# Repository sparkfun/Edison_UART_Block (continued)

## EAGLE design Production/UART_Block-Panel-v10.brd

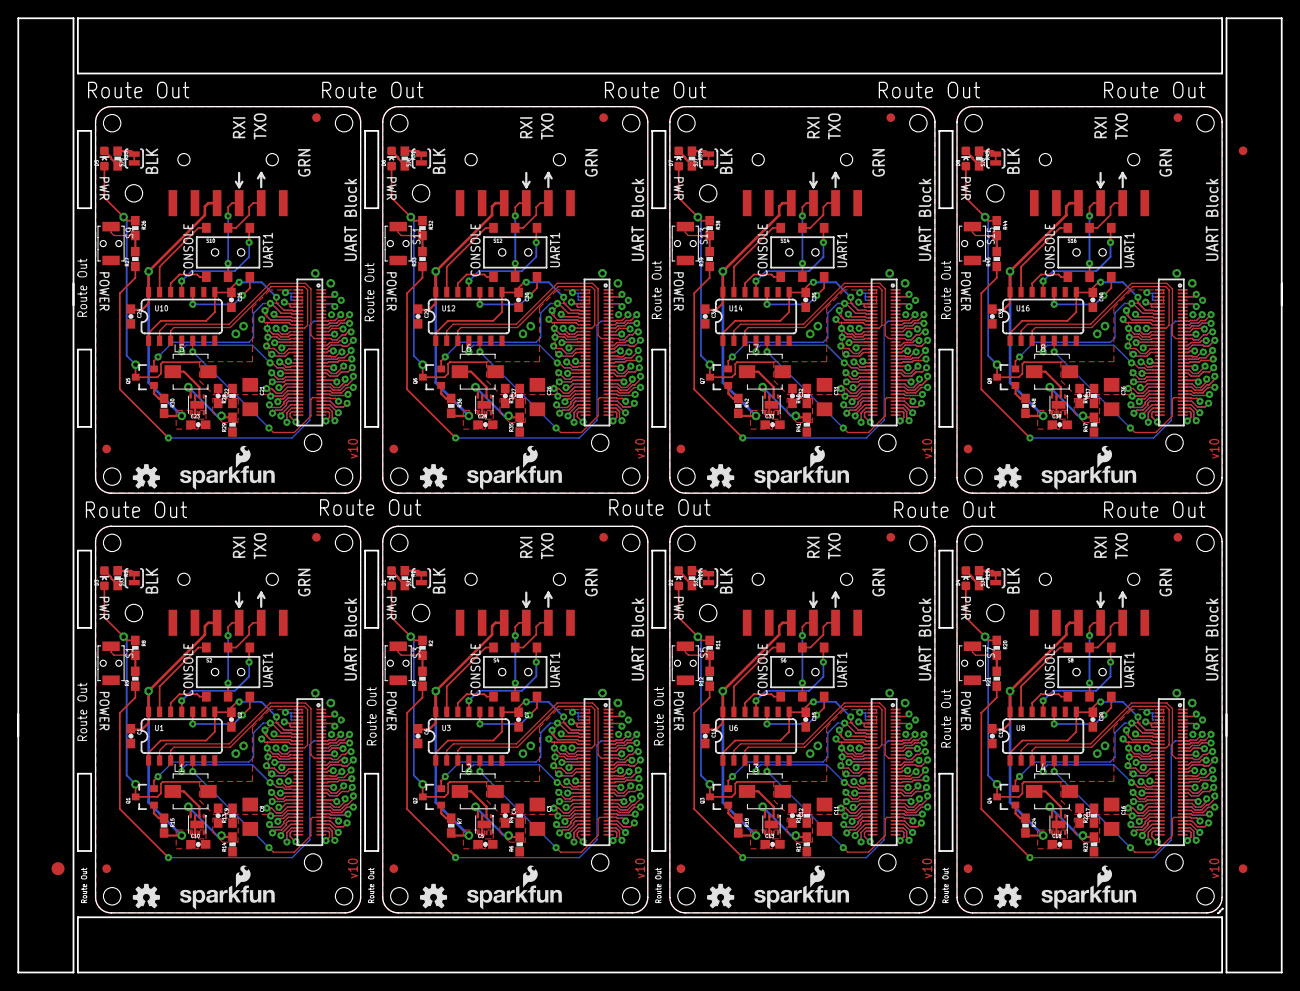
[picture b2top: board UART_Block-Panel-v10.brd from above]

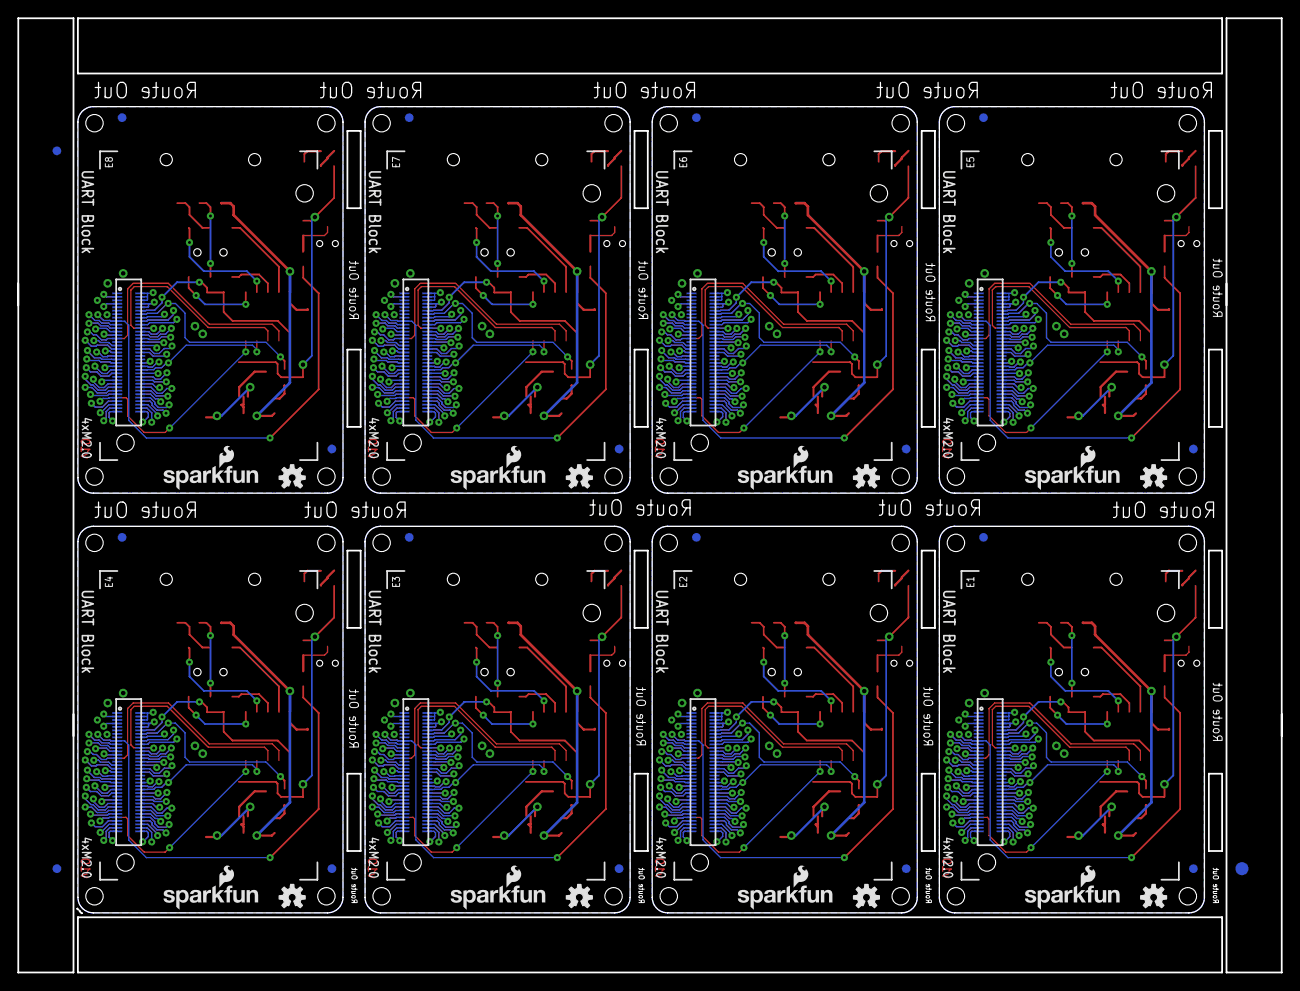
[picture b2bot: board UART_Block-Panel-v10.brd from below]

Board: 2 copper layers, 145.3 x 109.7 mm, 246 parts (51 on the bottom side), 568 nets.

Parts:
C1, C2, C6, C7, C14, C15, C19, C20, C24, C25, C29, C30, C34, C35, C39, C40: 0.1uF; 0603-CAP
C3, C8, C11, C16, C21, C26, C31, C36: 10uF; 1206
C4, C9, C12, C17, C22, C27, C32, C37: 47pF; 0603-CAP
C5, C10, C13, C18, C23, C28, C33, C38: 4.7uF; 0603-CAP
D1, D2, D3, D4, D5, D6, D7, D8: BLUE; LED-0603
E1, E2, E3, E4, E5, E6, E7, E8: EDISON_CONNECTOR_FULLMOUNTING_HOLES; EDISON_DAUGHTER
E$1, E$2: FIDUCIAL-1.5X3
E$3, E$4, E$5, E$6: FIDUCIAL-1X2
FID1, FID2, FID3, FID4, FID5, FID6, FID7, FID8, FID9, FID10, FID11, FID12, FID13, FID14, FID15, FID16, FID17, FID18, FID19, FID20, FID21, FID22, FID23, FID24, FID25, FID26, FID27, FID28, FID29, FID30, FID31, FID32: FIDUCIAL1X2; FIDUCIAL-1X2
JP1, JP2, JP3, JP4, JP5, JP6, JP7, JP8: 1X06-SMD
L1, L2, L3, L4, L5, L6, L7, L8: INDUCTOR-SRP4020
LOGO1, LOGO3, LOGO6, LOGO7, LOGO10, LOGO11, LOGO14, LOGO15, LOGO18, LOGO19, LOGO22, LOGO23, LOGO26, LOGO27, LOGO30, LOGO31: SFE_LOGO_NAME_FLAME.1_INCH; SFE_LOGO_NAME_FLAME_.1
LOGO2, LOGO4, LOGO5, LOGO8, LOGO9, LOGO12, LOGO13, LOGO16, LOGO17, LOGO20, LOGO21, LOGO24, LOGO25, LOGO28, LOGO29, LOGO32: OSHW-LOGOS; OSHW-LOGO-S
Q1, Q2, Q3, Q4, Q5, Q6, Q7, Q8: BSS138; SOT23-3
R1, R5, R7, R10, R15, R18, R19, R24, R25, R30, R31, R36, R37, R42, R43, R48: 1K; 0603-RES
R2, R8, R11, R20, R26, R32, R38, R44: 10K; 0603-RES
R3, R9, R12, R21, R27, R33, R39, R45: 22; 0603-RES
R4, R13, R16, R22, R28, R34, R40, R46: 680k; 0603-RES
R6, R14, R17, R23, R29, R35, R41, R47: 120k; 0603-RES
S1, S3, S5, S7, S9, S11, S13, S15: POWER; TACTILE_SWITCH-SMD-RIGHT-ANGLE
S2, S4, S6, S8, S10, S12, S14, S16: DPDT; AYZ0202
SJ1, SJ2, SJ3, SJ4, SJ5, SJ6, SJ7, SJ8: JUMPER-PAD-2-NC_BY_TRACE; PAD-JUMPER-2-NC_BY_TRACE_YES_SILK
U1, U3, U6, U8, U10, U12, U14, U16: SO14
U2, U4, U5, U7, U9, U11, U13, U15: TPS62065; WSON-8-PAD
U$1, U$2, U$3, U$4, U$5, U$6, U$7, U$8: EDISON_CONNECTOR_FULLHEADER; DF40C-70DP-0.4(51)

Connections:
1.8V: C2.1, E1.12, U1.1, U1.8, U$3.12
1.8V1: C7.1, E2.12, U3.1, U3.8, U$1.12
1.8V2: C15.1, E3.12, U6.1, U6.8, U$2.12
1.8V3: C20.1, E4.12, U8.1, U8.8, U$4.12
1.8V4: C25.1, E5.12, U10.1, U10.8, U$5.12
1.8V5: C30.1, E6.12, U12.1, U12.8, U$6.12
1.8V6: C35.1, E7.12, U14.1, U14.8, U$7.12
1.8V7: C40.1, E8.12, U16.1, U16.8, U$8.12
3.3V: E1.8, E1.10, U$3.8, U$3.10
3.3V1: E2.8, E2.10, U$1.8, U$1.10
3.3V2: E3.8, E3.10, U$2.8, U$2.10
3.3V3: E4.8, E4.10, U$4.8, U$4.10
3.3V4: E5.8, E5.10, U$5.8, U$5.10
3.3V5: E6.8, E6.10, U$6.8, U$6.10
3.3V6: E7.8, E7.10, U$7.8, U$7.10
3.3V7: E8.8, E8.10, U$8.8, U$8.10
DCIN: E1.14, Q1.2, U$3.14
DCIN1: E2.14, Q2.2, U$1.14
DCIN2: E3.14, Q3.2, U$2.14
DCIN3: E4.14, Q4.2, U$4.14
DCIN4: E5.14, Q5.2, U$5.14
DCIN5: E6.14, Q6.2, U$6.14
DCIN6: E7.14, Q7.2, U$7.14
DCIN7: E8.14, Q8.2, U$8.14
FAULT: E1.19, U$3.19
FAULT1: E2.19, U$1.19
FAULT2: E3.19, U$2.19
FAULT3: E4.19, U$4.19
FAULT4: E5.19, U$5.19
FAULT5: E6.19, U$6.19
FAULT6: E7.19, U$7.19
FAULT7: E8.19, U$8.19
FW_RCVR: E1.69, U$3.69
FW_RCVR1: E2.69, U$1.69
FW_RCVR2: E3.69, U$2.69
FW_RCVR3: E4.69, U$4.69
FW_RCVR4: E5.69, U$5.69
FW_RCVR5: E6.69, U$6.69
FW_RCVR6: E7.69, U$7.69
FW_RCVR7: E8.69, U$8.69
GND: C1.2, C2.2, C8.2, C10.2, E1.1, E1.5, E1.9, E1.11, E1.13, E1.15, JP2.5, JP2.6, R14.1, S1.2, SJ3.1, U1.7, U4.1, U4.3, U4.6, U4.PAD, U$3.1, U$3.5, U$3.9, U$3.11, U$3.13, U$3.15
GND1: C3.2, C5.2, C6.2, C7.2, E2.1, E2.5, E2.9, E2.11, E2.13, E2.15, JP1.5, JP1.6, R6.1, S3.2, SJ1.1, U2.1, U2.3, U2.6, U2.PAD, U3.7, U$1.1, U$1.5, U$1.9, U$1.11, U$1.13, U$1.15
GND2: C11.2, C13.2, C14.2, C15.2, E3.1, E3.5, E3.9, E3.11, E3.13, E3.15, JP3.5, JP3.6, R17.1, S5.2, SJ2.1, U5.1, U5.3, U5.6, U5.PAD, U6.7, U$2.1, U$2.5, U$2.9, U$2.11, U$2.13, U$2.15
GND3: C16.2, C18.2, C19.2, C20.2, E4.1, E4.5, E4.9, E4.11, E4.13, E4.15, JP4.5, JP4.6, R23.1, S7.2, SJ4.1, U7.1, U7.3, U7.6, U7.PAD, U8.7, U$4.1, U$4.5, U$4.9, U$4.11, U$4.13, U$4.15
GND4: C21.2, C23.2, C24.2, C25.2, E5.1, E5.5, E5.9, E5.11, E5.13, E5.15, JP5.5, JP5.6, R29.1, S9.2, SJ5.1, U9.1, U9.3, U9.6, U9.PAD, U10.7, U$5.1, U$5.5, U$5.9, U$5.11, U$5.13, U$5.15
GND5: C26.2, C28.2, C29.2, C30.2, E6.1, E6.5, E6.9, E6.11, E6.13, E6.15, JP6.5, JP6.6, R35.1, S11.2, SJ6.1, U11.1, U11.3, U11.6, U11.PAD, U12.7, U$6.1, U$6.5, U$6.9, U$6.11, U$6.13, U$6.15
GND6: C31.2, C33.2, C34.2, C35.2, E7.1, E7.5, E7.9, E7.11, E7.13, E7.15, JP7.5, JP7.6, R41.1, S13.2, SJ7.1, U13.1, U13.3, U13.6, U13.PAD, U14.7, U$7.1, U$7.5, U$7.9, U$7.11, U$7.13, U$7.15
GND7: C36.2, C38.2, C39.2, C40.2, E8.1, E8.5, E8.9, E8.11, E8.13, E8.15, JP8.5, JP8.6, R47.1, S15.2, SJ8.1, U15.1, U15.3, U15.6, U15.PAD, U16.7, U$8.1, U$8.5, U$8.9, U$8.11, U$8.13, U$8.15
GP1: E2.48, U$1.48
GP2: E2.42, U$1.42
GP3: E2.34, U$1.34
GP4: E2.32, U$1.32
GP5: E2.30, U$1.30
GP6: E2.28, U$1.28
GP7: E2.26, U$1.26
GP8: E2.25, U$1.25
GP9: E2.24, U$1.24
GP10: E3.48, U$2.48
GP11: E3.42, U$2.42
GP12: E3.34, U$2.34
GP12_PWM0: E1.35, U$3.35
GP12_PWM1: E2.35, U$1.35
GP12_PWM2: E3.35, U$2.35
GP12_PWM3: E4.35, U$4.35
GP12_PWM4: E5.35, U$5.35
GP12_PWM5: E6.35, U$6.35
GP12_PWM6: E7.35, U$7.35
GP12_PWM7: E8.35, U$8.35
GP13: E3.32, U$2.32
GP13_PWM1: E1.33, U$3.33
GP13_PWM2: E2.33, U$1.33
GP13_PWM3: E3.33, U$2.33
GP13_PWM4: E4.33, U$4.33
GP13_PWM5: E5.33, U$5.33
GP13_PWM6: E6.33, U$6.33
GP13_PWM7: E7.33, U$7.33
GP13_PWM8: E8.33, U$8.33
GP14: E1.48, U$3.48
GP15: E1.42, U$3.42
GP16: E3.30, U$2.30
GP17: E3.28, U$2.28
GP18: E3.26, U$2.26
GP19: E3.25, U$2.25
GP19_I2C_1_SCL: E1.41, U$3.41
GP19_I2C_1_SCL1: E2.41, U$1.41
GP19_I2C_1_SCL2: E3.41, U$2.41
GP19_I2C_1_SCL3: E4.41, U$4.41
GP19_I2C_1_SCL4: E5.41, U$5.41
GP19_I2C_1_SCL5: E6.41, U$6.41
GP19_I2C_1_SCL6: E7.41, U$7.41
GP19_I2C_1_SCL7: E8.41, U$8.41
GP20: E3.24, U$2.24
GP20_I2C_1_SDA: E1.43, U$3.43
GP20_I2C_1_SDA1: E2.43, U$1.43
GP20_I2C_1_SDA2: E3.43, U$2.43
GP20_I2C_1_SDA3: E4.43, U$4.43
GP20_I2C_1_SDA4: E5.43, U$5.43
GP20_I2C_1_SDA5: E6.43, U$6.43
GP20_I2C_1_SDA6: E7.43, U$7.43
GP20_I2C_1_SDA7: E8.43, U$8.43
GP21: E4.48, U$4.48
GP22: E4.42, U$4.42
GP23: E4.34, U$4.34
GP24: E4.32, U$4.32
GP25: E4.30, U$4.30
GP26: E4.28, U$4.28
GP27: E4.26, U$4.26
GP27_I2C_6_SCL: E1.45, U$3.45
GP27_I2C_6_SCL1: E2.45, U$1.45
GP27_I2C_6_SCL2: E3.45, U$2.45
GP27_I2C_6_SCL3: E4.45, U$4.45
GP27_I2C_6_SCL4: E5.45, U$5.45
GP27_I2C_6_SCL5: E6.45, U$6.45
GP27_I2C_6_SCL6: E7.45, U$7.45
GP27_I2C_6_SCL7: E8.45, U$8.45
GP28: E4.25, U$4.25
GP28_I2C_6_SDA: E1.47, U$3.47
GP28_I2C_6_SDA1: E2.47, U$1.47
GP28_I2C_6_SDA2: E3.47, U$2.47
GP28_I2C_6_SDA3: E4.47, U$4.47
GP28_I2C_6_SDA4: E5.47, U$5.47
GP28_I2C_6_SDA5: E6.47, U$6.47
GP28_I2C_6_SDA6: E7.47, U$7.47
GP28_I2C_6_SDA7: E8.47, U$8.47
GP29: E4.24, U$4.24
GP30: E5.48, U$5.48
GP31: E5.42, U$5.42
GP32: E5.34, U$5.34
GP33: E5.32, U$5.32
GP34: E5.30, U$5.30
GP35: E5.28, U$5.28
GP36: E5.26, U$5.26
GP37: E5.25, U$5.25
GP38: E5.24, U$5.24
GP39: E6.48, U$6.48
GP40: E6.42, U$6.42
GP40_I2S_2_CLK: E1.52, U$3.52
GP40_I2S_2_CLK1: E2.52, U$1.52
GP40_I2S_2_CLK2: E3.52, U$2.52
GP40_I2S_2_CLK3: E4.52, U$4.52
GP40_I2S_2_CLK4: E5.52, U$5.52
GP40_I2S_2_CLK5: E6.52, U$6.52
GP40_I2S_2_CLK6: E7.52, U$7.52
GP40_I2S_2_CLK7: E8.52, U$8.52
GP41: E6.34, U$6.34
GP41_I2S_2_FS: E1.54, U$3.54
GP41_I2S_2_FS1: E2.54, U$1.54
GP41_I2S_2_FS2: E3.54, U$2.54
GP41_I2S_2_FS3: E4.54, U$4.54
GP41_I2S_2_FS4: E5.54, U$5.54
GP41_I2S_2_FS5: E6.54, U$6.54
GP41_I2S_2_FS6: E7.54, U$7.54
GP41_I2S_2_FS7: E8.54, U$8.54
GP42: E6.32, U$6.32
GP42_I2S_2_RXD: E1.50, U$3.50
GP42_I2S_2_RXD1: E2.50, U$1.50
GP42_I2S_2_RXD2: E3.50, U$2.50
GP42_I2S_2_RXD3: E4.50, U$4.50
GP42_I2S_2_RXD4: E5.50, U$5.50
GP42_I2S_2_RXD5: E6.50, U$6.50
GP42_I2S_2_RXD6: E7.50, U$7.50
GP42_I2S_2_RXD7: E8.50, U$8.50
GP43: E6.30, U$6.30
GP43_I2S_2_TXD: E1.56, U$3.56
GP43_I2S_2_TXD1: E2.56, U$1.56
GP43_I2S_2_TXD2: E3.56, U$2.56
GP43_I2S_2_TXD3: E4.56, U$4.56
GP43_I2S_2_TXD4: E5.56, U$5.56
GP43_I2S_2_TXD5: E6.56, U$6.56
GP43_I2S_2_TXD6: E7.56, U$7.56
GP43_I2S_2_TXD7: E8.56, U$8.56
GP44: E1.24, U$3.24
GP45: E1.26, U$3.26
GP46: E1.28, U$3.28
GP47: E1.30, U$3.30
GP48: E1.32, U$3.32
GP49: E1.34, U$3.34
GP50: E6.28, U$6.28
GP51: E6.26, U$6.26
GP52: E6.25, U$6.25
GP53: E6.24, U$6.24
GP54: E7.48, U$7.48
GP55: E7.42, U$7.42
GP56: E7.34, U$7.34
GP57: E7.32, U$7.32
GP58: E7.30, U$7.30
GP59: E7.28, U$7.28
GP60: E7.26, U$7.26
GP61: E7.25, U$7.25
GP62: E7.24, U$7.24
GP63: E8.48, U$8.48
GP64: E8.42, U$8.42
GP65: E8.34, U$8.34
GP66: E8.32, U$8.32
GP67: E8.30, U$8.30
GP68: E8.28, U$8.28
GP69: E8.26, U$8.26
GP70: E8.25, U$8.25
GP71: E8.24, U$8.24
GP77_SD_0_CD#: E1.60, U$3.60
GP77_SD_0_CD#1: E2.60, U$1.60
GP77_SD_0_CD#2: E3.60, U$2.60
GP77_SD_0_CD#3: E4.60, U$4.60
GP77_SD_0_CD#4: E5.60, U$5.60
GP77_SD_0_CD#5: E6.60, U$6.60
GP77_SD_0_CD#6: E7.60, U$7.60
GP77_SD_0_CD#7: E8.60, U$8.60
GP78_SD_0_CLK: E1.58, U$3.58
GP78_SD_0_CLK1: E2.58, U$1.58
GP78_SD_0_CLK2: E3.58, U$2.58
GP78_SD_0_CLK3: E4.58, U$4.58
GP78_SD_0_CLK4: E5.58, U$5.58
GP78_SD_0_CLK5: E6.58, U$6.58
GP78_SD_0_CLK6: E7.58, U$7.58
GP78_SD_0_CLK7: E8.58, U$8.58
GP79_SD_0_CMD: E1.62, U$3.62
GP79_SD_0_CMD1: E2.62, U$1.62
GP79_SD_0_CMD2: E3.62, U$2.62
GP79_SD_0_CMD3: E4.62, U$4.62
GP79_SD_0_CMD4: E5.62, U$5.62
GP79_SD_0_CMD5: E6.62, U$6.62
GP79_SD_0_CMD6: E7.62, U$7.62
GP79_SD_0_CMD7: E8.62, U$8.62
GP80_SD_0_DAT0: E1.66, U$3.66
GP80_SD_0_DAT1: E2.66, U$1.66
GP80_SD_0_DAT2: E3.66, U$2.66
GP80_SD_0_DAT3: E4.66, U$4.66
GP80_SD_0_DAT4: E5.66, U$5.66
GP80_SD_0_DAT5: E6.66, U$6.66
GP80_SD_0_DAT6: E7.66, U$7.66
GP80_SD_0_DAT7: E8.66, U$8.66
GP81_SD_0_DAT1: E1.70, U$3.70
GP81_SD_0_DAT2: E2.70, U$1.70
GP81_SD_0_DAT3: E3.70, U$2.70
GP81_SD_0_DAT4: E4.70, U$4.70
GP81_SD_0_DAT5: E5.70, U$5.70
GP81_SD_0_DAT6: E6.70, U$6.70
GP81_SD_0_DAT7: E7.70, U$7.70
GP81_SD_0_DAT8: E8.70, U$8.70
GP82_SD_0_DAT1: E2.64, U$1.64
GP82_SD_0_DAT2: E1.64, U$3.64
GP82_SD_0_DAT3: E3.64, U$2.64
GP82_SD_0_DAT4: E4.64, U$4.64
GP82_SD_0_DAT5: E5.64, U$5.64
GP82_SD_0_DAT6: E6.64, U$6.64
GP82_SD_0_DAT7: E7.64, U$7.64
GP82_SD_0_DAT8: E8.64, U$8.64
GP83_SD_0_DAT1: E2.68, U$1.68
GP83_SD_0_DAT2: E3.68, U$2.68
GP83_SD_0_DAT3: E1.68, U$3.68
GP83_SD_0_DAT4: E4.68, U$4.68
GP83_SD_0_DAT5: E5.68, U$5.68
GP83_SD_0_DAT6: E6.68, U$6.68
GP83_SD_0_DAT7: E7.68, U$7.68
GP83_SD_0_DAT8: E8.68, U$8.68
GP84_SD_CLK_FB: E1.44, U$3.44
GP84_SD_CLK_FB1: E2.44, U$1.44
GP84_SD_CLK_FB2: E3.44, U$2.44
GP84_SD_CLK_FB3: E4.44, U$4.44
GP84_SD_CLK_FB4: E5.44, U$5.44
GP84_SD_CLK_FB5: E6.44, U$6.44
GP84_SD_CLK_FB6: E7.44, U$7.44
GP84_SD_CLK_FB7: E8.44, U$8.44
GP109_SPI_2_CLK: E1.55, U$3.55
GP109_SPI_2_CLK1: E2.55, U$1.55
GP109_SPI_2_CLK2: E3.55, U$2.55
GP109_SPI_2_CLK3: E4.55, U$4.55
GP109_SPI_2_CLK4: E5.55, U$5.55
GP109_SPI_2_CLK5: E6.55, U$6.55
GP109_SPI_2_CLK6: E7.55, U$7.55
GP109_SPI_2_CLK7: E8.55, U$8.55
GP110_SPI_2_FS0: E1.53, U$3.53
GP110_SPI_2_FS1: E2.53, U$1.53
GP110_SPI_2_FS2: E3.53, U$2.53
GP110_SPI_2_FS3: E4.53, U$4.53
GP110_SPI_2_FS4: E5.53, U$5.53
GP110_SPI_2_FS5: E6.53, U$6.53
GP110_SPI_2_FS6: E7.53, U$7.53
GP110_SPI_2_FS7: E8.53, U$8.53
GP111_SPI_2_FS1: E1.51, U$3.51
GP111_SPI_2_FS2: E2.51, U$1.51
GP111_SPI_2_FS3: E3.51, U$2.51
GP111_SPI_2_FS4: E4.51, U$4.51
GP111_SPI_2_FS5: E5.51, U$5.51
GP111_SPI_2_FS6: E6.51, U$6.51
GP111_SPI_2_FS7: E7.51, U$7.51
GP111_SPI_2_FS8: E8.51, U$8.51
GP114_SPI_2_RXD: E1.59, U$3.59
GP114_SPI_2_RXD1: E2.59, U$1.59
GP114_SPI_2_RXD2: E3.59, U$2.59
GP114_SPI_2_RXD3: E4.59, U$4.59
GP114_SPI_2_RXD4: E5.59, U$5.59
GP114_SPI_2_RXD5: E6.59, U$6.59
GP114_SPI_2_RXD6: E7.59, U$7.59
GP114_SPI_2_RXD7: E8.59, U$8.59
GP115_SPI_2_TXD: E1.57, U$3.57
GP115_SPI_2_TXD1: E2.57, U$1.57
GP115_SPI_2_TXD2: E3.57, U$2.57
GP115_SPI_2_TXD3: E4.57, U$4.57
GP115_SPI_2_TXD4: E5.57, U$5.57
GP115_SPI_2_TXD5: E6.57, U$6.57
GP115_SPI_2_TXD6: E7.57, U$7.57
GP115_SPI_2_TXD7: E8.57, U$8.57
GP128_UART_1_CTS: E1.65, U$3.65
GP128_UART_1_CTS1: E2.65, U$1.65
GP128_UART_1_CTS2: E3.65, U$2.65
GP128_UART_1_CTS3: E4.65, U$4.65
GP128_UART_1_CTS4: E5.65, U$5.65
GP128_UART_1_CTS5: E6.65, U$6.65
GP128_UART_1_CTS6: E7.65, U$7.65
GP128_UART_1_CTS7: E8.65, U$8.65
GP129_UART_1_RTS: E1.63, U$3.63
GP129_UART_1_RTS1: E2.63, U$1.63
GP129_UART_1_RTS2: E3.63, U$2.63
GP129_UART_1_RTS3: E4.63, U$4.63
GP129_UART_1_RTS4: E5.63, U$5.63
GP129_UART_1_RTS5: E6.63, U$6.63
GP129_UART_1_RTS6: E7.63, U$7.63
GP129_UART_1_RTS7: E8.63, U$8.63
GP130_UART_1_RX: E1.61, U1.5, U$3.61
GP130_UART_1_RX1: E2.61, U3.5, U$1.61
GP130_UART_1_RX2: E3.61, U6.5, U$2.61
GP130_UART_1_RX3: E4.61, U8.5, U$4.61
GP130_UART_1_RX4: E5.61, U10.5, U$5.61
GP130_UART_1_RX5: E6.61, U12.5, U$6.61
GP130_UART_1_RX6: E7.61, U14.5, U$7.61
GP130_UART_1_RX7: E8.61, U16.5, U$8.61
GP131_UART_1_TX: E1.46, U1.4, U$3.46
GP131_UART_1_TX1: E2.46, U3.4, U$1.46
GP131_UART_1_TX2: E3.46, U6.4, U$2.46
GP131_UART_1_TX3: E4.46, U8.4, U$4.46
GP131_UART_1_TX4: E5.46, U10.4, U$5.46
GP131_UART_1_TX5: E6.46, U12.4, U$6.46
GP131_UART_1_TX6: E7.46, U14.4, U$7.46
GP131_UART_1_TX7: E8.46, U16.4, U$8.46
GP134_UART_2_RX: E1.22, U1.3, U$3.22
GP134_UART_2_RX1: E2.22, U3.3, U$1.22
GP134_UART_2_RX2: E3.22, U6.3, U$2.22
GP134_UART_2_RX3: E4.22, U8.3, U$4.22
GP134_UART_2_RX4: E5.22, U10.3, U$5.22
GP134_UART_2_RX5: E6.22, U12.3, U$6.22
GP134_UART_2_RX6: E7.22, U14.3, U$7.22
GP134_UART_2_RX7: E8.22, U16.3, U$8.22
GP135_UART_2_TX: E1.27, U1.2, U$3.27
GP135_UART_2_TX1: E2.27, U3.2, U$1.27
GP135_UART_2_TX2: E3.27, U6.2, U$2.27
GP135_UART_2_TX3: E4.27, U8.2, U$4.27
GP135_UART_2_TX4: E5.27, U10.2, U$5.27
GP135_UART_2_TX5: E6.27, U12.2, U$6.27
GP135_UART_2_TX6: E7.27, U14.2, U$7.27
GP135_UART_2_TX7: E8.27, U16.2, U$8.27
GP165: E1.25, U$3.25
GP182_PWM1: E2.37, U$1.37
GP182_PWM2: E1.37, U$3.37
GP182_PWM3: E3.37, U$2.37
GP182_PWM4: E4.37, U$4.37
GP182_PWM5: E5.37, U$5.37
GP182_PWM6: E6.37, U$6.37
GP182_PWM7: E7.37, U$7.37
GP182_PWM8: E8.37, U$8.37
GP183_PWM1: E2.39, U$1.39
GP183_PWM2: E3.39, U$2.39
GP183_PWM3: E1.39, U$3.39
GP183_PWM4: E4.39, U$4.39
GP183_PWM5: E5.39, U$5.39
GP183_PWM6: E6.39, U$6.39
GP183_PWM7: E7.39, U$7.39
GP183_PWM8: E8.39, U$8.39
MSIC_SLP_CLK: E1.7, U$3.7
MSIC_SLP_CLK1: E2.7, U$1.7
MSIC_SLP_CLK2: E3.7, U$2.7
MSIC_SLP_CLK3: E4.7, U$4.7
MSIC_SLP_CLK4: E5.7, U$5.7
MSIC_SLP_CLK5: E6.7, U$6.7
MSIC_SLP_CLK6: E7.7, U$7.7
MSIC_SLP_CLK7: E8.7, U$8.7
unnamed: Q1.1, R15.1
unnamed: D1.C, R1.2
unnamed: R1.1, SJ1.2
unnamed: R2.2, R3.2, S3.1
unnamed: C4.2, R4.1, R6.2, U2.4
unnamed: L2.P$1, U2.2
unnamed: Q2.1, R7.1
unnamed: D2.C, R10.2
unnamed: R10.1, SJ2.2
unnamed: R11.2, R12.2, S5.1
unnamed: C12.2, R16.1, R17.2, U5.4
unnamed: D3.C, R5.2
unnamed: R5.1, SJ3.2
unnamed: L3.P$1, U5.2
unnamed: R8.2, R9.2, S1.1
unnamed: Q3.1, R18.1
unnamed: D4.C, R19.2
unnamed: C9.2, R13.1, R14.2, U4.4
unnamed: L1.P$1, U4.2
unnamed: R19.1, SJ4.2
unnamed: R20.2, R21.2, S7.1
unnamed: C17.2, R22.1, R23.2, U7.4
unnamed: L4.P$1, U7.2
unnamed: Q4.1, R24.1
unnamed: D5.C, R25.2
unnamed: R25.1, SJ5.2
unnamed: R26.2, R27.2, S9.1
unnamed: C22.2, R28.1, R29.2, U9.4
unnamed: L5.P$1, U9.2
unnamed: Q5.1, R30.1
unnamed: D6.C, R31.2
unnamed: R31.1, SJ6.2
unnamed: R32.2, R33.2, S11.1
unnamed: C27.2, R34.1, R35.2, U11.4
unnamed: L6.P$1, U11.2
unnamed: Q6.1, R36.1
unnamed: D7.C, R37.2
unnamed: R37.1, SJ7.2
unnamed: R38.2, R39.2, S13.1
unnamed: C32.2, R40.1, R41.2, U13.4
unnamed: L7.P$1, U13.2
unnamed: Q7.1, R42.1
unnamed: D8.C, R43.2
unnamed: R43.1, SJ8.2
unnamed: R44.2, R45.2, S15.1
unnamed: C37.2, R46.1, R47.2, U15.4
unnamed: L8.P$1, U15.2
unnamed: Q8.1, R48.1
OSC_CLK_OUT: E1.67, U$3.67
OSC_CLK_OUT1: E2.67, U$1.67
OSC_CLK_OUT2: E3.67, U$2.67
OSC_CLK_OUT3: E4.67, U$4.67
OSC_CLK_OUT4: E5.67, U$5.67
OSC_CLK_OUT5: E6.67, U$6.67
OSC_CLK_OUT6: E7.67, U$7.67
OSC_CLK_OUT7: E8.67, U$8.67
PSW: E1.21, U$3.21
PSW1: E2.21, U$1.21
PSW2: E3.21, U$2.21
PSW3: E4.21, U$4.21
PSW4: E5.21, U$5.21
PSW5: E6.21, U$6.21
PSW6: E7.21, U$7.21
PSW7: E8.21, U$8.21
PWRBTN#: E1.17, R9.1, U$3.17
PWRBTN#1: E2.17, R3.1, U$1.17
PWRBTN#2: E3.17, R12.1, U$2.17
PWRBTN#3: E4.17, R21.1, U$4.17
PWRBTN#4: E5.17, R27.1, U$5.17
PWRBTN#5: E6.17, R33.1, U$6.17
PWRBTN#6: E7.17, R39.1, U$7.17
PWRBTN#7: E8.17, R45.1, U$8.17
RCVR_MODE: E1.31, U$3.31
RCVR_MODE1: E2.31, U$1.31
RCVR_MODE2: E3.31, U$2.31
RCVR_MODE3: E4.31, U$4.31
RCVR_MODE4: E5.31, U$5.31
RCVR_MODE5: E6.31, U$6.31
RCVR_MODE6: E7.31, U$7.31
RCVR_MODE7: E8.31, U$8.31
RESET_OUT#: E1.36, U$3.36
RESET_OUT#1: E2.36, U$1.36
RESET_OUT#2: E3.36, U$2.36
RESET_OUT#3: E4.36, U$4.36
RESET_OUT#4: E5.36, U$5.36
RESET_OUT#5: E6.36, U$6.36
RESET_OUT#6: E7.36, U$7.36
RESET_OUT#7: E8.36, U$8.36
RXI: JP2.3, S2.5
RXI1: JP1.3, S4.5
RXI2: JP3.3, S6.5
RXI3: JP4.3, S8.5
RXI4: JP5.3, S10.5
RXI5: JP6.3, S12.5
RXI6: JP7.3, S14.5
RXI7: JP8.3, S16.5
TXO: JP2.2, S2.2
TXO1: JP1.2, S4.2
TXO2: JP3.2, S6.2
TXO3: JP4.2, S8.2
TXO4: JP5.2, S10.2
TXO5: JP6.2, S12.2
TXO6: JP7.2, S14.2
TXO7: JP8.2, S16.2
UART1RX: S2.6, U1.10
UART1RX1: S4.6, U3.10
UART1RX2: S6.6, U6.10
UART1RX3: S8.6, U8.10
UART1RX4: S10.6, U10.10
UART1RX5: S12.6, U12.10
UART1RX6: S14.6, U14.10
UART1RX7: S16.6, U16.10
UART1TX: S2.3, U1.11
UART1TX1: S4.3, U3.11
UART1TX2: S6.3, U6.11
UART1TX3: S8.3, U8.11
UART1TX4: S10.3, U10.11
UART1TX5: S12.3, U12.11
UART1TX6: S14.3, U14.11
UART1TX7: S16.3, U16.11
UART2RX: S2.4, U1.12
UART2RX1: S4.4, U3.12
UART2RX2: S6.4, U6.12
UART2RX3: S8.4, U8.12
UART2RX4: S10.4, U10.12
UART2RX5: S12.4, U12.12
UART2RX6: S14.4, U14.12
UART2RX7: S16.4, U16.12
UART2TX: S2.1, U1.13
UART2TX1: S4.1, U3.13
UART2TX2: S6.1, U6.13
UART2TX3: S8.1, U8.13
UART2TX4: S10.1, U10.13
UART2TX5: S12.1, U12.13
UART2TX6: S14.1, U14.13
UART2TX7: S16.1, U16.13
USB_DN: E1.18, U$3.18
USB_DN1: E2.18, U$1.18
USB_DN2: E3.18, U$2.18
USB_DN3: E4.18, U$4.18
USB_DN4: E5.18, U$5.18
USB_DN5: E6.18, U$6.18
USB_DN6: E7.18, U$7.18
USB_DN7: E8.18, U$8.18
USB_DP: E1.16, U$3.16
USB_DP1: E2.16, U$1.16
USB_DP2: E3.16, U$2.16
USB_DP3: E4.16, U$4.16
USB_DP4: E5.16, U$5.16
USB_DP5: E6.16, U$6.16
USB_DP6: E7.16, U$7.16
USB_DP7: E8.16, U$8.16
USB_ID: E1.3, U$3.3
USB_ID1: E2.3, U$1.3
USB_ID2: E3.3, U$2.3
USB_ID3: E4.3, U$4.3
USB_ID4: E5.3, U$5.3
USB_ID5: E6.3, U$6.3
USB_ID6: E7.3, U$7.3
USB_ID7: E8.3, U$8.3
USB_VBUS: E1.20, U$3.20
USB_VBUS1: E2.20, U$1.20
USB_VBUS2: E3.20, U$2.20
USB_VBUS3: E4.20, U$4.20
USB_VBUS4: E5.20, U$5.20
USB_VBUS5: E6.20, U$6.20
USB_VBUS6: E7.20, U$7.20
USB_VBUS7: E8.20, U$8.20
VCC: C1.1, C10.1, JP2.4, R15.2, U1.14, U4.5, U4.7, U4.8
VCC1: C5.1, C6.1, JP1.4, R7.2, U2.5, U2.7, U2.8, U3.14
VCC2: C13.1, C14.1, JP3.4, R18.2, U5.5, U5.7, U5.8, U6.14
VCC3: C18.1, C19.1, JP4.4, R24.2, U7.5, U7.7, U7.8, U8.14
VCC4: C23.1, C24.1, JP5.4, R30.2, U9.5, U9.7, U9.8, U10.14
VCC5: C28.1, C29.1, JP6.4, R36.2, U11.5, U11.7, U11.8, U12.14
VCC6: C33.1, C34.1, JP7.4, R42.2, U13.5, U13.7, U13.8, U14.14
VCC7: C38.1, C39.1, JP8.4, R48.2, U15.5, U15.7, U15.8, U16.14
VSYS: C8.1, C9.1, D3.A, E1.2, E1.4, E1.6, L1.P$2, Q1.3, R8.1, R13.2, U$3.2, U$3.4, U$3.6
VSYS1: C3.1, C4.1, D1.A, E2.2, E2.4, E2.6, L2.P$2, Q2.3, R2.1, R4.2, U$1.2, U$1.4, U$1.6
VSYS2: C11.1, C12.1, D2.A, E3.2, E3.4, E3.6, L3.P$2, Q3.3, R11.1, R16.2, U$2.2, U$2.4, U$2.6
VSYS3: C16.1, C17.1, D4.A, E4.2, E4.4, E4.6, L4.P$2, Q4.3, R20.1, R22.2, U$4.2, U$4.4, U$4.6
VSYS4: C21.1, C22.1, D5.A, E5.2, E5.4, E5.6, L5.P$2, Q5.3, R26.1, R28.2, U$5.2, U$5.4, U$5.6
VSYS5: C26.1, C27.1, D6.A, E6.2, E6.4, E6.6, L6.P$2, Q6.3, R32.1, R34.2, U$6.2, U$6.4, U$6.6
VSYS6: C31.1, C32.1, D7.A, E7.2, E7.4, E7.6, L7.P$2, Q7.3, R38.1, R40.2, U$7.2, U$7.4, U$7.6
VSYS7: C36.1, C37.1, D8.A, E8.2, E8.4, E8.6, L8.P$2, Q8.3, R44.1, R46.2, U$8.2, U$8.4, U$8.6
V_BAT_BKUP: E1.23, U$3.23
V_BAT_BKUP1: E2.23, U$1.23
V_BAT_BKUP2: E3.23, U$2.23
V_BAT_BKUP3: E4.23, U$4.23
V_BAT_BKUP4: E5.23, U$5.23
V_BAT_BKUP5: E6.23, U$6.23
V_BAT_BKUP6: E7.23, U$7.23
V_BAT_BKUP7: E8.23, U$8.23
